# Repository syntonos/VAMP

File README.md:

# VAMP | by synotonos

**Sample, synthesize, VAMP.** 

An experimental, intuitive sampler synth, based with Daisy Seed 3. Pocket sized and equipped with an onboard sampling mic.

## About
A VAMP is a repeated four-chord progression. A vampire is a creature of myth that drinks blood, probably among other things. 

**VAMP by syntonos** is a play on both of those definitions. Take the lifeblood of a sound, then build a creature of your own with it. Built for field sampling and on-the-go chord construction, with an onboard microphone and headphone port.

At its most basic, I'd like it to be able to take a sample and pitch shift it to match each of the octave's keys + modulation with sampling and playback with the knobs & joystick (time dilation, pitch, reverb, distortion, sampling bitrate). There would also be a looper. (I'm coding this already, it should be done by the time the build is approved, but I do need the physical sampler to test the code.) At its best (might take a while for me to research the music theory and then code), I'd like for it to be able to recognize chords based on keys played and then have the joystick be able to modify it (inversions, substitutions, etc). It would be an interesting way to apply polyphony and sampling, and it would make VAMP a unique, experimental chord builder.

This whole set of synths is mostly because I do want to make music, and I want an instrument that works for me. I'm also very interested in digital signal processing, and this teaches both. Inspired by a ton of samplers currenly out (AKAI MPC Sample, CHOMPI, PO33-KO). I wanted this to be portable and pocketable, and this technically is if you have big pockets. (Also working on a tiny little portable battery to accompany this, it currently can be used attached to any USB-C 5V 1A source).

## Features
- 8-note keyboard + 4 layers to toggle through.
- 4 rotary encoders + an analog joystick for sound modulation. 
- 0.91" OLED display.
- Five 3.5mm TRS ports: MIDI IN, INSTRUMENT IN, LINE IN, LINE OUT, USB-C Power + Data.
- 3.5mm headphone jack. 
- Onboard omnidirectional stereo microphone with additional LINE IN options.
- Up to ten minutes of sampling time with the Daisy Seed. 
- USB-C 5V 1A power. 

## Assembly Instructions + Flashing Firmware
### Soldering
Solder in the:
- 16x Keyswitches
    - Throughhole. Line up the pins with SW1 - 16, then solder the pins into place.

- 4x Rotary Encoders EC11 Half 15mm
    - Throughhole. Align the pins, secure the encoder through the mounting pins, and solder the pins into place.

- 1x 0.91" OLED Display
    - Make sure the pins match the labels on the silkscreen or the PCB (Top to Bottom: SDA SCK 3V3 GND). Solder the pins into place.

- 2x MEMS Microphones 
    - Located on the back of the PCB, right below the Daisy Seed 3. Tin each of the exposed pads. Make sure your connections do not short. Then press the SMT mic into the pads. Again, make sure none of your connections short. Use a hot plate or a reflow oven as needed.

- OPTIONAL 1x SD Card Module
    - Located on the bottom side of the PCB, below the OLED display module. Align the module so that it's facing up, then insert the pins (check that the nets are correct) then solder them in. 

## PCB
### 3D Models

### Schematic

### PCB Layout

### Firmware
Follow the Daisy Seed's instructions for flashing firmware [Electro Smith](https://electro-smith.github.io/libDaisy/md_doc_2md_2__a7___getting-_started-_daisy-_bootloader.html). Firmware found in the folder firmware. FLASH THROUGH THE DAISY BOOTLOADER. THIS REQUIRES THE RAM.

## BOM
- 1x PCB + PCBA (topside)
- 1x Daisy Seed 3
- 1x 0.91" OLED Display Module
- 4x Rotary Encoders EC11 15mm Half
- 4x Rotary Encoder Caps (White for default)
- 16x Kaihl Choc V2 Low Profile Switches (Deep Sea Whale for default)
- 16x 3D Printed Keycaps (Choc Spacing)

## BOM Expanded
- 1x PCB + PCBA (topside)
    - $189.61 + tariffs ([JLCPCB](https://jlcpcb.com/))
- 1x Daisy Seed 3
    - $29.99 + shipping [ElectroSmith](https://daisy.audio/products/seed3)
- 1x 0.91" OLED Display Module
    - $6.88 [Amazon](https://www.amazon.com/Screen-128x32-Display-SSD1306-Arduino/dp/B0DZGLN4FK?sr=8-4)
- 4x Rotary Encoders EC11 15mm Half
    - $8.44 [Amazon](https://www.amazon.com/Uxcell-Rotary-Encoder-Button-Components/dp/B0177VGSQY?sr=8-7)
- 4x Rotary Encoder Caps (White for default)
    - $0.99 per unit [Aliexpress](https://www.aliexpress.us/item/3256802787455407.html?spm=a2g0o.productlist.main.16.5f933d7aKUXwsp&algo_pvid=06b1b22b-34d8-4d1f-a808-07da94751539&algo_exp_id=06b1b22b-34d8-4d1f-a808-07da94751539-15&pdp_ext_f=%7B%22order%22%3A%221236%22%2C%22eval%22%3A%221%22%2C%22fromPage%22%3A%22search%22%7D&pdp_npi=6%40dis%21USD%212.17%210.99%21%21%2114.54%216.65%21%402103128817871075013327626e0d51%2112000056642379111%21sea%21US%210%21ABX%211%210%21n_tag%3A-29910%3Bd%3A84f82c56%3Bm03_new_user%3A-29895%3BpisId%3A5000000210792318&curPageLogUid=D3d2l73Dyr8M&utparam-url=scene%3Asearch%7Cquery_from%3A%7Cx_object_id%3A1005002973770159%7C_p_origin_prod%3A)
- 16x Kaihl Choc V2 Low Profile Switches (Deep Sea Whale for default)
    - $29.90 [Amazon](https://www.amazon.com/Deep-Sea-Switches-Mechanical-Keyboard/dp/B0F8NLZQQD?sr=8-5)
- 16x 3D Printed Keycaps (Choc Spacing)
    - $depends [Printables, full credit to MementoArgonaut
@MementoArgona_889573](https://www.printables.com/model/1254489-kailh-choc-v2-ergonomic-sculpted-keycaps/files)
- 1x 3D Printed Joystick Cap
    - $depends [Printables, full credit to Taro Hayashi
@TaroHayashi_2240460](https://www.printables.com/model/1083436-joystick-cap)

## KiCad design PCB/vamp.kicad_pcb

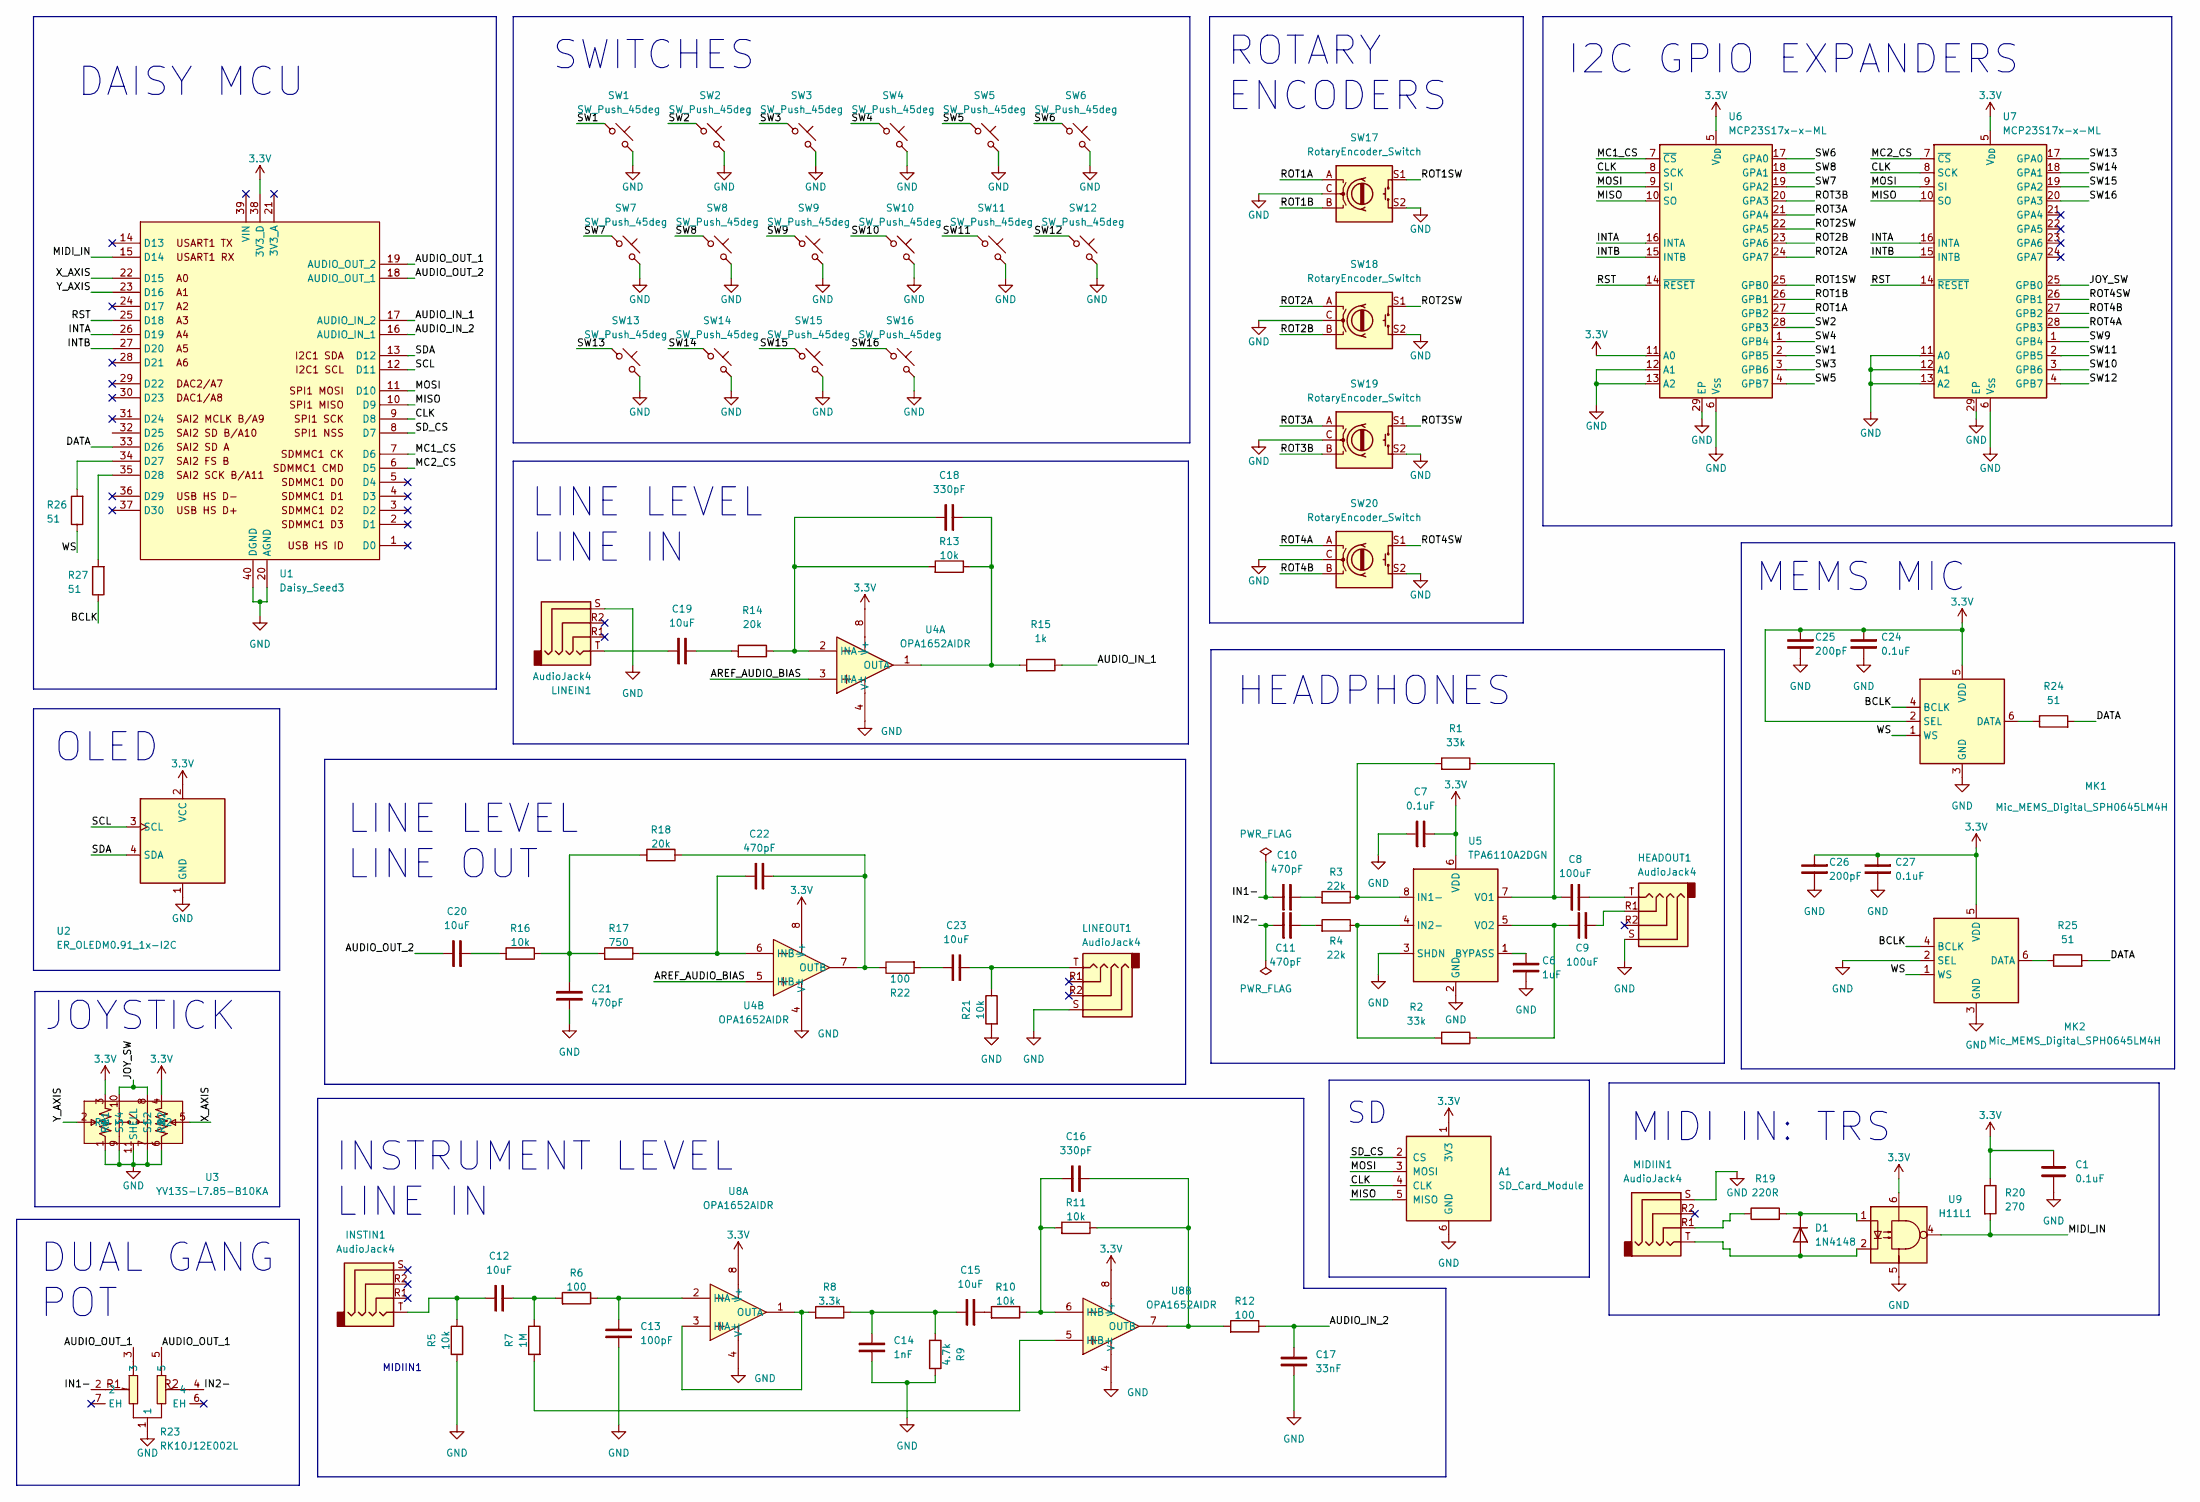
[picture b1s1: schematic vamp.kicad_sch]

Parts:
A1: SD_Card_Module
C1, C7, C24, C27: 0.1uF; C_0603_1608Metric
C6: 1uF; C_0603_1608Metric
C8, C9: 100uF; C_0603_1608Metric
C10, C11, C21, C22: 470pF; C_0603_1608Metric
C12, C15, C19, C20, C23: 10uF; C_0603_1608Metric
C13: 100pF; C_0603_1608Metric
C14: 1nF; C_0603_1608Metric
C16, C18: 330pF; C_0603_1608Metric
C17: 33nF; C_0603_1608Metric
C25, C26: 200pF; C_0603_1608Metric
D1: 1N4148; D_SOD-123
HEADOUT1: AudioJack4; Jack_3.5mm_PJ320D_Horizontal_3D
INSTIN1: AudioJack4; Jack_3.5mm_PJ320D_Horizontal_3D
LINEIN1: AudioJack4; Jack_3.5mm_PJ320D_Horizontal_3D
LINEOUT1: AudioJack4; Jack_3.5mm_PJ320D_Horizontal_3D
MIDIIN1: AudioJack4; Jack_3.5mm_PJ320D_Horizontal_3D
MK1, MK2: Mic_MEMS_Digital_SPH0645LM4H; Mic_MEMS_Digital_Knowles_SPH0645LM4H
R1, R2: 33k; R_0603_1608Metric
R3, R4: 22k; R_0603_1608Metric
R5, R10, R11, R13, R16, R21: 10k; R_0603_1608Metric
R6, R12, R22: 100; R_0603_1608Metric
R7: 1M; R_0603_1608Metric
R8: 3.3k; R_0603_1608Metric
R9: 4.7k; R_0603_1608Metric
R14, R18: 20k; R_0603_1608Metric
R15: 1k; R_0603_1608Metric
R17: 750; R_0603_1608Metric
R19: 220R; C_0603_1608Metric
R20: 270; C_0603_1608Metric
R23: RK10J12E002L; RES-TH_RK10J12E002L; MPN RK10J12E002L; LCSC Part C231765
R24, R25, R26, R27: 51; C_0603_1608Metric
SW1, SW2, SW3, SW4, SW5, SW6, SW7, SW8, SW9, SW10, SW11, SW12, SW13, SW14, SW15, SW16: SW_Push_45deg; SW_choc_v2_1u
SW17, SW18, SW19, SW20: RotaryEncoder_Switch; RotaryEncoder_Alps_EC12E-Switch_Vertical_H20mm
U1: Daisy_Seed3; DAISY_SEED
U2: ER_OLEDM0.91_1x-I2C
U3: YV13S-L7.85-B10KA; JOYTICK-TH_YV13S-L7.85-B10KA-60--0-DL01; MPN YV13S-L7.85-B10Ka(60)-0-DL01; LCSC Part C37323747
U4, U8: OPA1652AIDR; SOIC-8_L5.0-W4.0-P1.27-LS6.0-BL; MPN OPA1652AIDR; LCSC Part C30025
U5: TPA6110A2DGN; HVSSOP-8-1EP_3x3mm_P0.65mm_EP1.57x1.89mm
U6, U7: MCP23S17x-x-ML; QFN-28-1EP_6x6mm_P0.65mm_EP4.25x4.25mm
U9: H11L1; IC_H11L1SM

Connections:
3.3V: A1.1 (3V3), C1.1, C7.1, C24.1, C25.1, C26.1, C27.1, MK1.2 (SEL), MK1.5 (VDD), MK2.5 (VDD), R20.1, U1.38 (3V3_D), U2.2 (VCC), U3.3 (R1), U3.4 (R2), U4.8 (V+), U5.6 (VDD), U6.5 (V_{DD}), U6.11 (A0), U7.5 (V_{DD}), U8.8 (V+), U9.6
/AREF_AUDIO_BIAS: U4.3 (INA+), U4.5 (INB+)
/AUDIO_IN_1: R15.2, U1.17 (AUDIO_IN_2)
/AUDIO_IN_2: C17.2, R12.2, U1.16 (AUDIO_IN_1)
/AUDIO_OUT_1: R23.3, R23.5, U1.19 (AUDIO_OUT_2)
/AUDIO_OUT_2: C20.2, U1.18 (AUDIO_OUT_1)
/BCLK: MK1.4 (BCLK), MK2.4 (BCLK), R27.1
/CLK: A1.4 (CLK), U1.9 (D8), U6.8 (SCK), U7.8 (SCK)
/DATA: R24.2, R25.2, U1.33 (D26)
/IN1-: C10.2, R23.2
/IN2-: C11.2, R23.4
/INTA: U1.26 (D19), U6.16 (INTA), U7.16 (INTA)
/INTB: U1.27 (D20), U6.15 (INTB), U7.15 (INTB)
/JOY_SW: U3.8 (S2), U3.10 (S4), U7.25 (GPB0)
/MC1_CS: U1.7 (D6), U6.7 (~CS)
/MC2_CS: U1.6 (D5), U7.7 (~CS)
/MIDI_IN: R20.2, U1.15 (D14), U9.4
/MISO: A1.5 (MISO), U1.10 (D9), U6.10 (SO), U7.10 (SO)
/MOSI: A1.3 (MOSI), U1.11 (D10), U6.9 (SI), U7.9 (SI)
/ROT1A: SW17.A, U6.27 (GPB2)
/ROT1B: SW17.B, U6.26 (GPB1)
/ROT1SW: SW17.S1, U6.25 (GPB0)
/ROT2A: SW18.A, U6.24 (GPA7)
/ROT2B: SW18.B, U6.23 (GPA6)
/ROT2SW: SW18.S1, U6.22 (GPA5)
/ROT3A: SW19.A, U6.21 (GPA4)
/ROT3B: SW19.B, U6.20 (GPA3)
/ROT3SW: SW19.S1
/ROT4A: SW20.A, U7.28 (GPB3)
/ROT4B: SW20.B, U7.27 (GPB2)
/ROT4SW: SW20.S1, U7.26 (GPB1)
/RST: U1.25 (D18), U6.14 (~RESET), U7.14 (~RESET)
/SCL: U1.12 (D11), U2.3 (SCL)
/SDA: U1.13 (D12), U2.4 (SDA)
/SD_CS: A1.2 (CS), U1.8 (D7)
/SW1: SW1.1, U6.2 (GPB5)
/SW2: SW2.1, U6.28 (GPB3)
/SW3: SW3.1, U6.3 (GPB6)
/SW4: SW4.1, U6.1 (GPB4)
/SW5: SW5.1, U6.4 (GPB7)
/SW6: SW6.1, U6.17 (GPA0)
/SW7: SW7.1, U6.19 (GPA2)
/SW8: SW8.1, U6.18 (GPA1)
/SW9: SW9.1, U7.1 (GPB4)
/SW10: SW10.1, U7.3 (GPB6)
/SW11: SW11.1, U7.2 (GPB5)
/SW12: SW12.1, U7.4 (GPB7)
/SW13: SW13.1, U7.17 (GPA0)
/SW14: SW14.1, U7.18 (GPA1)
/SW15: SW15.1, U7.19 (GPA2)
/SW16: SW16.1, U7.20 (GPA3)
/WS: MK1.1 (WS), MK2.1 (WS), R26.1
/X_AXIS: U1.22 (D15), U3.5 (R2)
/Y_AXIS: U1.23 (D16), U3.2 (R1)
GND: A1.6 (GND), C1.2, C6.1, C7.2, C13.1, C14.1, C17.1, C21.1, C24.2, C25.2, C26.2, C27.2, HEADOUT1.S, LINEIN1.S, LINEOUT1.S, MIDIIN1.S, MK1.3 (GND), MK2.2 (SEL), MK2.3 (GND), R5.1, R9.2, R21.1, R23.1, SW1.2, SW2.2, SW3.2, SW4.2, SW5.2, SW6.2, SW7.2, SW8.2, SW9.2, SW10.2, SW11.2, SW12.2, SW13.2, SW14.2, SW15.2, SW16.2, SW17.C, SW17.S2, SW18.C, SW18.S2, SW19.C, SW19.S2, SW20.C, SW20.S2, U1.20 (AGND), U1.40 (DGND), U2.1 (GND), U3.1 (R1), U3.6 (R2), U3.7 (S1), U3.9 (S3), U3.11 (SHELL), U4.4 (V-), U5.2 (GND), U5.3 (SHDN), U5.9 (GND), U6.6 (V_{SS}), U6.12 (A1), U6.13 (A2), U6.29 (EP), U7.6 (V_{SS}), U7.11 (A0), U7.12 (A1), U7.13 (A2), U7.29 (EP), U8.4 (V-), U9.5
unnamed: C8.1, HEADOUT1.T
unnamed: C9.1, HEADOUT1.R1
unnamed: C10.1, R3.1
unnamed: C11.1, R4.1
unnamed: C12.1, R6.1, R7.2
unnamed: C12.2, INSTIN1.T, R5.2
unnamed: C14.2, C15.2, R8.2, R9.1
unnamed: C15.1, R10.1
unnamed: C19.1, R14.1
unnamed: C19.2, LINEIN1.T
unnamed: C20.1, R16.1
unnamed: C21.2, R16.2, R17.1, R18.1
unnamed: C23.1, LINEOUT1.T, R21.2
unnamed: C23.2, R22.1
unnamed: D1.2 (A), MIDIIN1.T, U9.2
unnamed: D1.1 (K), R19.2, U9.1
unnamed: MIDIIN1.R1, R19.1
unnamed: MK1.6 (DATA), R24.1
unnamed: MK2.6 (DATA), R25.1
unnamed: R26.2, U1.34 (D27)
unnamed: R27.2, U1.35 (D28)
unnamed: C18.2, R13.1, R14.2, U4.2 (INA-)
unnamed: C18.1, R13.2, R15.1, U4.1 (OUTA)
unnamed: C22.2, R17.2, U4.6 (INB-)
unnamed: C22.1, R18.2, R22.2, U4.7 (OUTB)
unnamed: C6.2, U5.1 (BYPASS)
unnamed: R1.1, R3.2, U5.8 (IN1-)
unnamed: R2.1, R4.2, U5.4 (IN2-)
unnamed: C8.2, R1.2, U5.7 (VO1)
unnamed: C9.2, R2.2, U5.5 (VO2)
unnamed: R8.1, U8.1 (OUTA), U8.3 (INA+)
unnamed: C13.2, R6.2, U8.2 (INA-)
unnamed: R7.1, U8.5 (INB+)
unnamed: C16.2, R10.2, R11.1, U8.6 (INB-)
unnamed: C16.1, R11.2, R12.1, U8.7 (OUTB)

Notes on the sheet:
MEMS MIC
MIDIIN1
ROTARY ENCODERS
MIDI IN: TRS
HEADPHONES
OLED
I2C GPIO EXPANDERS
LINE LEVEL LINE OUT
JOYSTICK
SWITCHES
DAISY MCU
INSTRUMENT LEVEL LINE IN
LINE LEVEL LINE IN
DUAL GANG POT

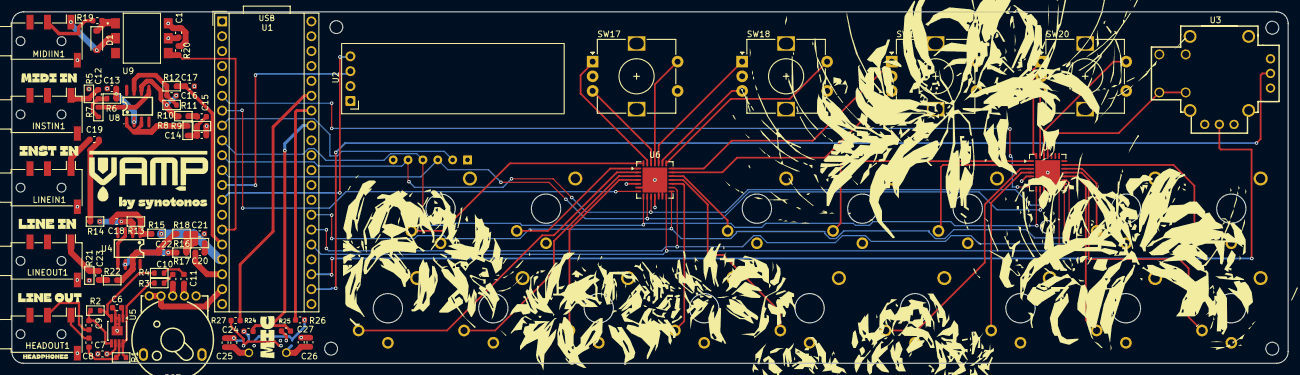
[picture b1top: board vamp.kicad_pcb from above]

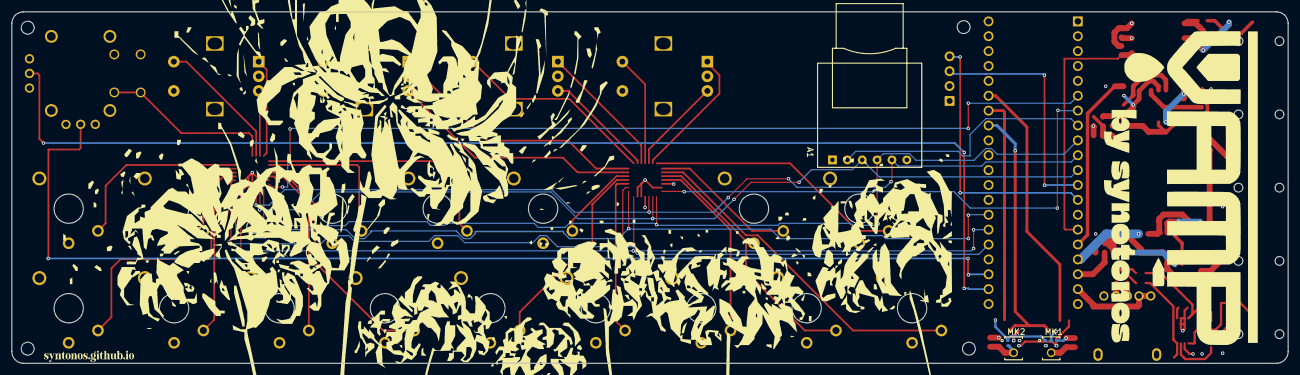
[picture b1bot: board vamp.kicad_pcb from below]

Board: 4 copper layers, 217.9 x 60.0 mm, 88 parts (3 on the bottom side), 89 nets.

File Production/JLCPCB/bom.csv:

Designator,Footprint,Quantity,Value,LCSC Part #
A1,SD_Card_Module,1,SD_Card_Module,
"C1, C24, C27, C7",0603,4,0.1uF,
"C10, C11, C21, C22",0603,4,470pF,
"C12, C15, C19, C20, C23",0603,5,10uF,
C13,0603,1,100pF,
C14,0603,1,1nF,
"C16, C18",0603,2,330pF,
C17,0603,1,33nF,
"C25, C26",0603,2,200pF,
C6,0603,1,1uF,
"C8, C9",0603,2,100uF,
D1,D_SOD-123,1,1N4148,
"HEADOUT1, INSTIN1, LINEIN1, LINEOUT1, MIDIIN1",Jack_3.5mm_PJ320D_Horizontal_3D,5,AudioJack4,
"MK1, MK2",Mic_MEMS_Digital_Knowles_SPH0645LM4H,2,Mic_MEMS_Digital_SPH0645LM4H,
"R1, R2",0603,2,33k,
"R10, R11, R13, R16, R21, R5",0603,6,10k,
"R12, R22, R6",0603,3,100,
"R14, R18",0603,2,20k,
R15,0603,1,1k,
R17,0603,1,750,
R19,0603,1,220R,
R20,0603,1,270,
R23,RES-TH_RK10J12E002L,1,RK10J12E002L,C231765
"R24, R25, R26, R27",0603,4,51,
"R3, R4",0603,2,22k,
R7,0603,1,1M,
R8,0603,1,3.3k,
R9,0603,1,4.7k,
"SW1, SW10, SW11, SW12, SW13, SW14, SW15, SW16, SW2, SW3, SW4, SW5, SW6, SW7, SW8, SW9",SW_choc_v2_1u,16,SW_Push_45deg,
"SW17, SW18, SW19, SW20",RotaryEncoder_Alps_EC12E-Switch_Vertical_H20mm,4,RotaryEncoder_Switch,
U1,DAISY_SEED,1,Daisy_Seed3,
U2,ER_OLEDM0.91_1x-I2C,1,ER_OLEDM0.91_1x-I2C,
U3,JOYTICK-TH_YV13S-L7.85-B10KA-60--0-DL01,1,YV13S-L7.85-B10KA,C37323747
"U4, U8",SOIC-8_L5.0-W4.0-P1.27-LS6.0-BL,2,OPA1652AIDR,C30025
U5,HVSSOP-8-1EP_3x3mm_P0.65mm_EP1.57x1.89mm,1,TPA6110A2DGN,
"U6, U7",QFN-28-1EP_6x6mm_P0.65mm_EP4.25x4.25mm,2,MCP23S17x-x-ML,
U9,IC_H11L1SM,1,H11L1,
